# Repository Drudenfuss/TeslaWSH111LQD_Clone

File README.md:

# TeslaWSH111LQD_Clone
Tesla WSH 111 LQD Clone

Operationsverstärker Nachbau für REM.

GNU GPLv3

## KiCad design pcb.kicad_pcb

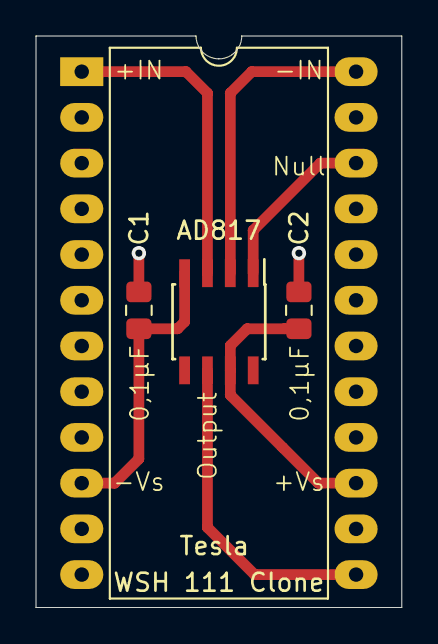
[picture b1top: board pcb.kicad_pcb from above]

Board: 2 copper layers, 20.3 x 31.8 mm, 4 parts (0 on the bottom side), 7 nets.

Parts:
AD817: LM741; SOIC-8_3.9x4.9mm_P1.27mm
C1, C2: 0,1 uF; C_0805_2012Metric_Pad1.15x1.40mm_HandSolder
Tesla: WSH 111 Clone; DIP-24_W15.24mm_LongPads

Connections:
+IN: AD817.3, Tesla.1
+Vs: AD817.7, C1.2, Tesla.15
-IN: AD817.2, Tesla.24
-Vs: AD817.4, C2.1, Tesla.10
GND: C1.1, C2.2, Tesla.3
NULL: AD817.1, Tesla.22
Output: AD817.6, Tesla.13
